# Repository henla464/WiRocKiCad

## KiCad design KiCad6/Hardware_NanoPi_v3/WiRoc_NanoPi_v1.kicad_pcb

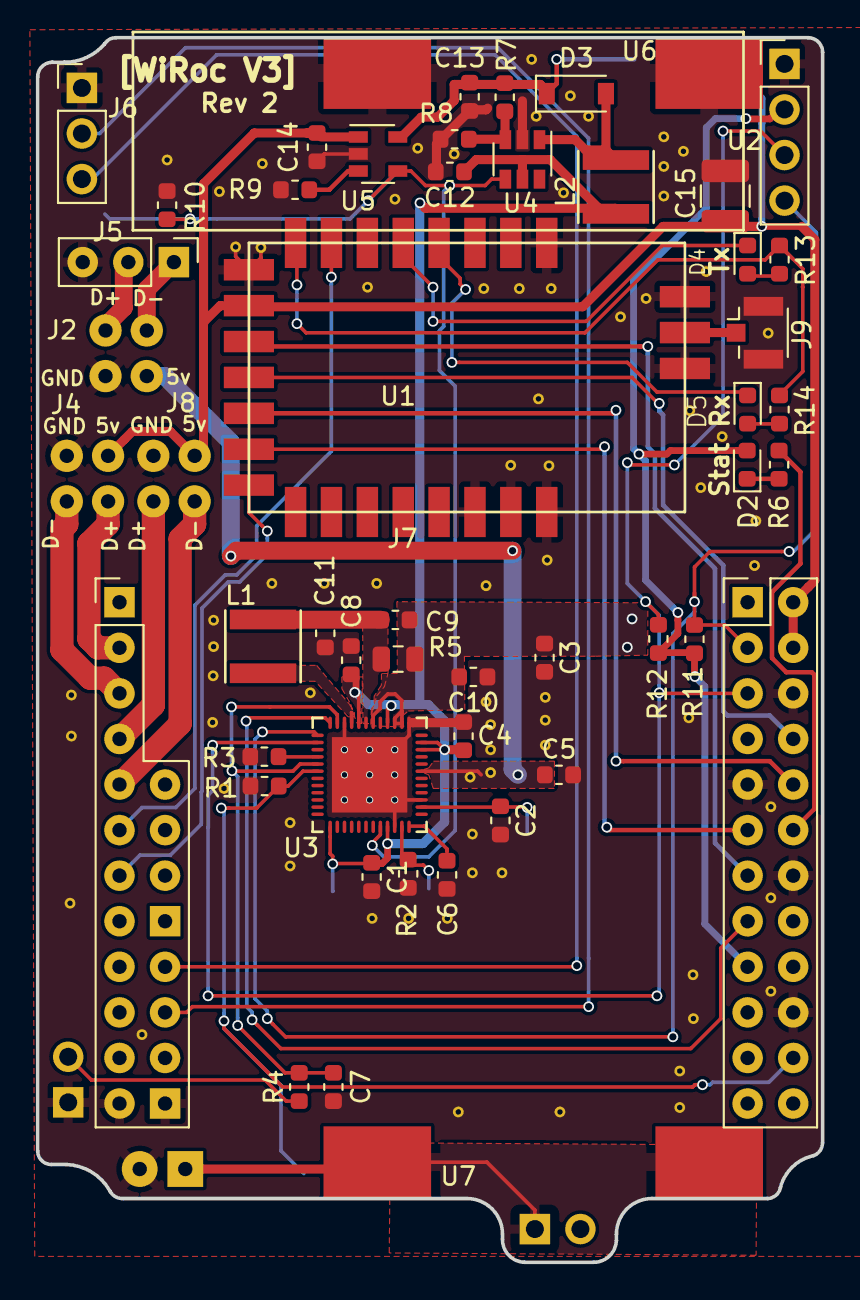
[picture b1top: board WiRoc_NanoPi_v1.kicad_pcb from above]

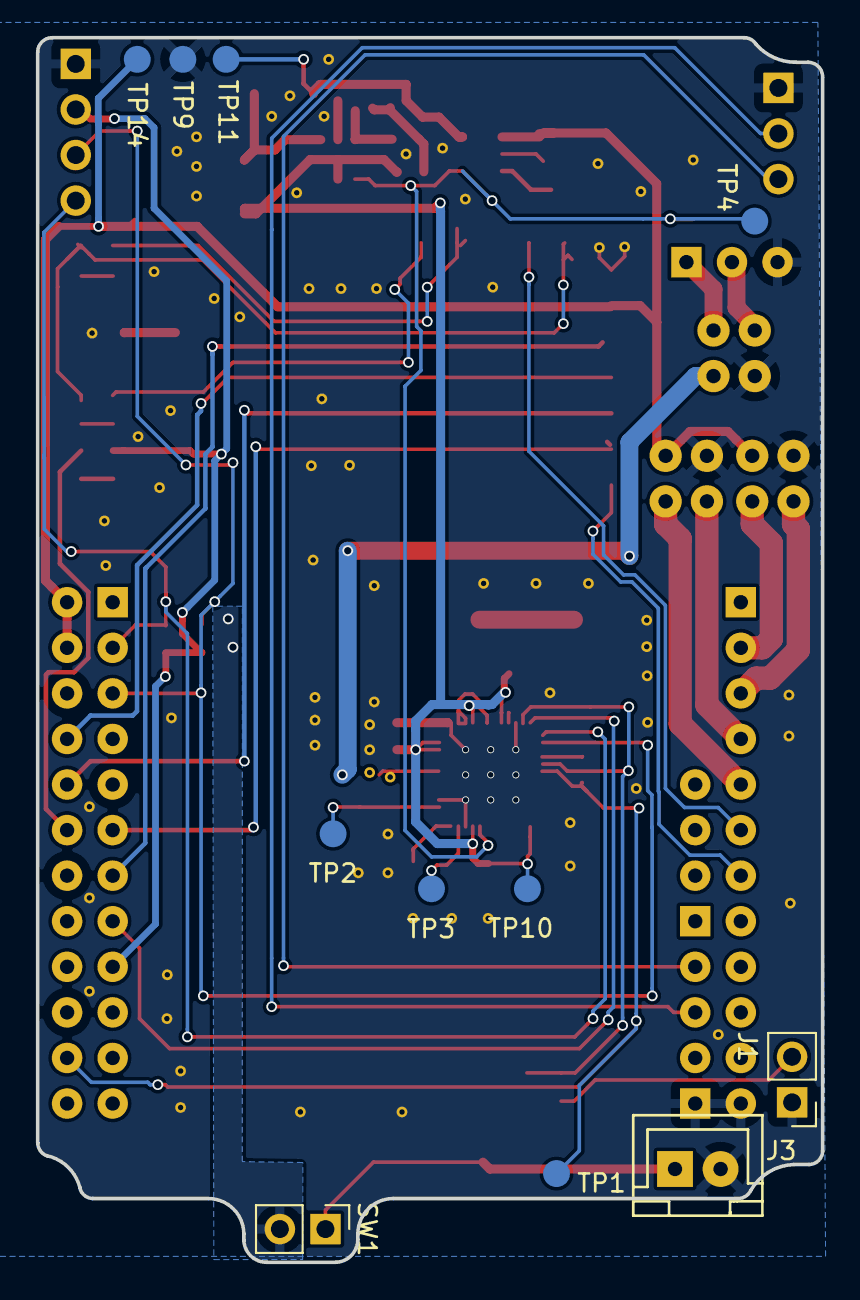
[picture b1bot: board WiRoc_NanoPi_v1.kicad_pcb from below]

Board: 2 copper layers, 43.8 x 68.3 mm, 60 parts (5 on the bottom side), 46 nets.

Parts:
C1, C3, C8, C10, C11: 4.7uF; C_0603_1608Metric
C2, C6, C9: 1uF; C_0603_1608Metric
C4, C5, C12, C13, C14: 10uF; C_0603_1608Metric
C7: 100pF; C_0603_1608Metric
C15: 47uF; C_1210_3225Metric
D2, D4, D5: LED; D_0603_1608Metric
D3: IN5819; D_SOD-123
J1: Conn_01x02; Pin_Header_Straight_1x02_Pitch2.54mm
J2: USB_Power_02x02; USBConnPads4
J3: JST-2PIN; JST_2.56
J4: USB_Host_Data_02x02; USBConnPads2
J5: Conn_01x03; Pin_Header_Straight_1x03_Pitch2.54mm
J6: HAT_Conn_DBG; Pin_Header_Straight_1x03_Pitch2.54mm
J7: NanoPIAir; NanoPiNeoAirAllPins
J8: USB_Host_Data_02x02; USBConnPads3
J9: Conn_Coaxial; U.FL_Hirose_U.FL-R-SMT-1_Vertical
L1, L2: 2.2uH-DCR<0.1R-1.5A; Inductor_SLW4018
R1, R10: 100K-1%; R_0603_1608Metric
R2, R3, R7: 200K-1%; R_0603_1608Metric
R4, R6, R13, R14: 1K; R_0603_1608Metric
R5: 0R03; R_0805_2012Metric
R8: 24K-1%; R_0603_1608Metric
R9: 3.6K-1%; R_0603_1608Metric
R11, R12: 10K; R_0603_1608Metric
SW1: SW_SPST; PinHeader_1x02_P2.54mm_Vertical
TP1, TP2, TP3, TP4, TP9, TP10, TP11, TP14: TEST; Measurement_Point_Round-SMD-Pad_Small
U1: DRF1268DS
U2: OLED; CONN_OLED_TWI-Socket_Strip_Straight_1x04_Pitch2.54mm
U3: AXP209; qfn48_6x6mm_Pitch0.4mm
U4: LP6226_SY7208; SOT-23-6
U5: SY6280; SOT-23-5
U6: BatteryPadM; BatteryPad
U7: BatteryPadP; BatteryPad

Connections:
BAT: C3.1, C9.1, C10.2, R5.2, SW1.2, U3.38, U3.39, U3.42
EXTEN: R10.2, TP4.1, U3.20, U4.4, U5.4
GND: C1.2, C2.2, C3.2, C4.2, C5.2, C6.2, C7.1, C8.1, C10.1, C11.1, C12.2, C13.2, C14.2, C15.1, J1.1, J2.4, J3.2, J4.4, J5.3, J6.1, J7.6, J7.9, J7.14, J7.20, J7.42, J7.51, J8.4, J9.2, R1.1, R2.1, R3.1, R8.1, R9.1, R10.1, TP9.1, U1.1, U1.9, U1.21, U1.22, U1.23, U1.24, U1.26, U2.1, U3.22, U3.27, U3.37, U3.46, U3.49, U4.2, U5.2, U6.1
IPSOUT: C1.1, C4.1, C8.2, C12.1, L2.1, TP10.1, U3.13, U3.21, U3.34, U3.35, U3.40, U3.44, U4.5
IRQ: J7.15, U3.48
LORAAUX: J7.11, U1.14
LORAEN: J7.13, U1.11
LORAMO: J7.37, U1.15
LORARS: J7.36, U1.7
N_VBUSEN: J7.22, R1.2, TP1.1, U3.6
unnamed: C2.1, TP2.1, U3.26
unnamed: C6.1, U3.24
unnamed: C9.2, C11.2, L1.2, R5.1, U3.43
unnamed: C13.1, D3.1, R7.2, TP11.1, U5.5
unnamed: D2.1, R6.1
unnamed: D3.2, L2.2, U4.1
unnamed: D4.1, U1.5
unnamed: D4.2, R13.1
unnamed: D5.1, U1.4
unnamed: D5.2, R14.1
unnamed: J1.2, R4.1
unnamed: J2.2, J5.1
unnamed: J2.3, J5.2
unnamed: J3.1, SW1.1, U7.1
unnamed: J6.2, J7.53
unnamed: J6.3, J7.54
unnamed: J9.1, U1.25
unnamed: L1.1, U3.45
unnamed: R2.2, TP3.1, U3.23
unnamed: R3.2, U3.4
unnamed: R7.1, R8.2, U4.3
unnamed: R9.2, U5.3
unnamed: R13.2, R14.2, U1.8
PWRON: C7.2, R4.2, U3.5, U3.47
SCK: J7.5, R12.1, U2.3, U3.2
SDA: J7.3, R11.1, U2.4, U3.1
STATUS_LED: J7.12, R6.2
SYS_3.3V: D2.2, J7.17, R11.2, R12.2, U2.2
UART1_RX: J7.10, U1.13
UART1_TX: J7.8, U1.12
USBHost-DM1: J4.2, J7.33
USBHost-DM2: J7.35, J8.2
USBHost-DP1: J4.3, J7.32
USBHost-DP2: J7.34, J8.3
VBUS: C5.1, J2.1, U3.31
VDD_5V: C14.1, C15.2, J4.1, J7.2, J7.4, J8.1, TP14.1, U1.10, U5.1

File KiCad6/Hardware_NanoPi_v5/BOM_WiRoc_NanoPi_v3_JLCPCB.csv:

Designator,Comment,Footprint,Comment2,LCSC Part #,Package
C13 C12 C14 C4 C5 ,10uF,Capacitor_SMD:C_0603_1608Metric, ,C19702,603
C3 ,4.7uF,Capacitor_SMD:C_0603_1608Metric, ,C19666,603
C9 C2 C6 ,1uF,Capacitor_SMD:C_0603_1608Metric, ,C15849,603
C11 C10 C8 C1 ,4.7uF,Capacitor_SMD:C_0603_1608Metric, ,C19666,603
C7 ,100pF,Capacitor_SMD:C_0603_1608Metric,100pF (101) ±5% 50V,C14858,603
C15 ,47uF,Capacitor_SMD:C_1210_3225Metric, ,C77101,1210
D3 ,IN5819,Diode_SMD:D_SOD-123,Diode Schottky 40V 1A Surface Mount SOD-123,C8597,SOD-123
D2 D5 D4 ,LED,Diode_SMD:D_0603_1608Metric,Red LED,C2286,603
J9 ,Conn_Coaxial,Connector_Coaxial:U.FL_Hirose_U.FL-R-SMT-1_Vertical, ,C88374, 
L2 L1 ,2.2uH-DCR<0.1R-1.5A,WiRoc:Inductor_SLW4018,FIXED IND 2.2UH 1.7A 55 MOHM SMD,C206341,4018
R7 R2 R3 ,200K-1%,Resistor_SMD:R_0603_1608Metric, ,C25811,603
R8 ,24K-1%,Resistor_SMD:R_0603_1608Metric, ,C23352,603
R9 ,3.6K-1%,Resistor_SMD:R_0603_1608Metric, ,C22980,603
R5 ,0R03,Resistor_SMD:R_0805_2012Metric,RESISTOR 0805 0.03Ω 1/8W±1%,C247605,805
R4 R6 R14 R13 ,1K,Resistor_SMD:R_0603_1608Metric,1KΩ (1001) ±1%,C21190,603
R1 R10 ,100K-1%,Resistor_SMD:R_0603_1608Metric, ,C25803,603
R11 R12 ,10K,Resistor_SMD:R_0603_1608Metric,RESISTOR 0603 10KΩ,C25804,603
U3 ,AXP209,WiRoc:qfn48_6x6mm_Pitch0.4mm,Enhanced single Cell Li-Battery and Power System Management IC,C80525,6mm x 6mm 48-pin QFN
U4 ,LP6226_SY7208,TO_SOT_Packages_SMD:SOT-23-6,High Efficiency Boost DC/DC Convertor,C80514,SOT23-6
U5 ,SY6280,TO_SOT_Packages_SMD:SOT-23-5,Power Distribution Switch  1In/1Out  Act-High Enable  1A  Vin 2.4÷5.5V  80mΩ,C55136,SOT23-5

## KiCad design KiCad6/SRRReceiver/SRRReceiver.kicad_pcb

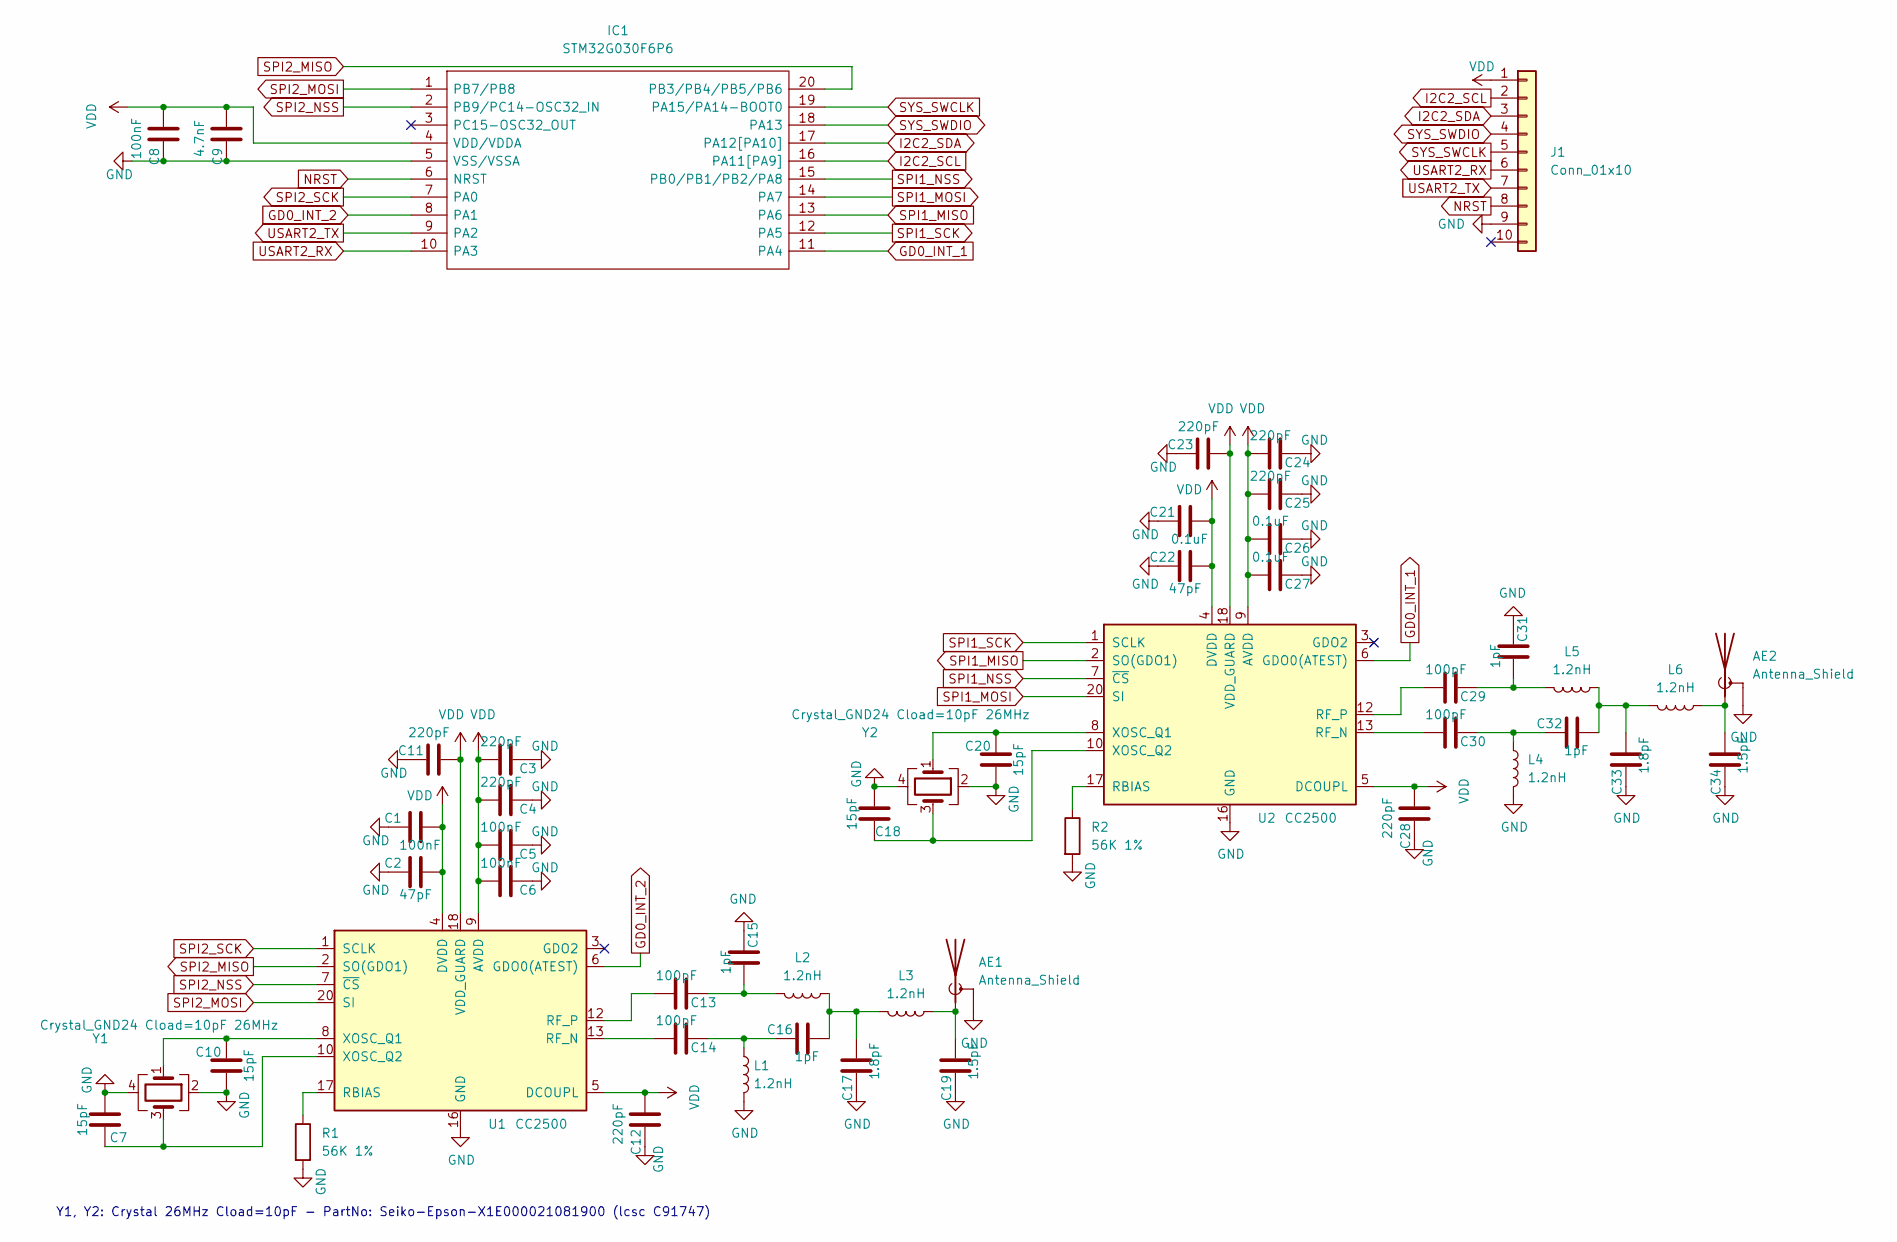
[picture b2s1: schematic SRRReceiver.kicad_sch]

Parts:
AE1, AE2: Antenna_Shield; Texas_SWRA117D_2.4GHz_Right
C1, C5, C6, C8: 100nF; C_0402_1005Metric; LCSC C1525
C2, C22: 47pF; C_0402_1005Metric; LCSC C1567
C3, C4, C11, C12, C23, C24, C25, C28: 220pF; C_0402_1005Metric; LCSC C16772
C7, C10, C18, C20: 15pF; C_0402_1005Metric; LCSC C1548
C9: 4.7nF; C_0402_1005Metric; LCSC C1538
C13, C14, C29, C30: 100pF; C_0402_1005Metric; LCSC C1546
C15, C16, C31, C32: 1pF; C_0402_1005Metric; LCSC C1550
C17, C33: 1.8pF; C_0402_1005Metric; LCSC C76902
C19, C34: 1.5pF; C_0402_1005Metric; LCSC C282238
C21, C26, C27: 0.1uF; C_0402_1005Metric; LCSC C1525
IC1: STM32G030F6P6; SOP65P640X120-20N; Manufacturer_Part_Number STM32G030F6P6; Mouser Part Number 511-STM32G030F6P6
J1: Conn_01x10; FPC-Connector_1x10-1MP_P0.5mm_Horizontal
L1, L2, L3, L4, L5, L6: 1.2nH; L_0402_1005Metric; LCSC C77117
R1, R2: 56K 1%; R_0402_1005Metric; LCSC C25796
U1, U2: CC2500; Texas_S-PVQFN-N20_EP2.4x2.4mm; LCSC C57494
Y1, Y2: Crystal_GND24 Cload=10pF 26MHz; Crystal_SMD_3225-4Pin_3.2x2.5mm; LCSC C91747

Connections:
GD0_INT_1: IC1.11 (PA4), U2.6 (GDO0(ATEST))
GD0_INT_2: IC1.8 (PA1), U1.6 (GDO0(ATEST))
GND: AE1.2 (Shield), AE2.2 (Shield), C1.1, C2.1, C3.1, C4.1, C5.1, C6.1, C7.1, C8.1, C9.1, C10.1, C11.1, C12.1, C15.1, C17.1, C18.1, C19.1, C20.1, C21.1, C22.1, C23.1, C24.1, C25.1, C26.1, C27.1, C28.1, C31.1, C33.1, C34.1, IC1.5 (VSS/VSSA), J1.9, L1.2, L4.2, R1.2, R2.2, U1.16 (GND), U1.19 (GND), U1.21 (GND), U2.16 (GND), U2.19 (GND), U2.21 (GND), Y1.2, Y1.4, Y2.2, Y2.4
I2C2_SCL: IC1.16 (PA11[PA9]), J1.2
I2C2_SDA: IC1.17 (PA12[PA10]), J1.3
NRST: IC1.6 (NRST), J1.8
unnamed: AE1.1 (A), C19.2, L3.1
unnamed: AE2.1 (A), C34.2, L6.1
unnamed: C7.2, U1.10 (XOSC_Q2), Y1.3
unnamed: C10.2, U1.8 (XOSC_Q1), Y1.1
unnamed: C13.1, C15.2, L2.2
unnamed: C13.2, U1.12 (RF_P)
unnamed: C14.1, C16.1, L1.1
unnamed: C14.2, U1.13 (RF_N)
unnamed: C16.2, C17.2, L2.1, L3.2
unnamed: C18.2, U2.10 (XOSC_Q2), Y2.3
unnamed: C20.2, U2.8 (XOSC_Q1), Y2.1
unnamed: C29.1, C31.2, L5.2
unnamed: C29.2, U2.12 (RF_P)
unnamed: C30.1, C32.1, L4.1
unnamed: C30.2, U2.13 (RF_N)
unnamed: C32.2, C33.2, L5.1, L6.2
unnamed: R1.1, U1.17 (RBIAS)
unnamed: R2.1, U2.17 (RBIAS)
SPI1_MISO: IC1.13 (PA6), U2.2 (SO(GDO1))
SPI1_MOSI: IC1.14 (PA7), U2.20 (SI)
SPI1_NSS: IC1.15 (PB0/PB1/PB2/PA8), U2.7 (~CS)
SPI1_SCK: IC1.12 (PA5), U2.1 (SCLK)
SPI2_MISO: IC1.20 (PB3/PB4/PB5/PB6), U1.2 (SO(GDO1))
SPI2_MOSI: IC1.1 (PB7/PB8), U1.20 (SI)
SPI2_NSS: IC1.2 (PB9/PC14-OSC32_IN), U1.7 (~CS)
SPI2_SCK: IC1.7 (PA0), U1.1 (SCLK)
SYS_SWCLK: IC1.19 (PA15/PA14-BOOT0), J1.5
SYS_SWDIO: IC1.18 (PA13), J1.4
USART2_RX: IC1.10 (PA3), J1.6
USART2_TX: IC1.9 (PA2), J1.7
VDD: C1.2, C2.2, C3.2, C4.2, C5.2, C6.2, C8.2, C9.2, C11.2, C12.2, C21.2, C22.2, C23.2, C24.2, C25.2, C26.2, C27.2, C28.2, IC1.4 (VDD/VDDA), J1.1, U1.4 (DVDD), U1.5 (DCOUPL), U1.9 (AVDD), U1.11 (AVDD), U1.14 (AVDD), U1.15 (AVDD), U1.18 (VDD_GUARD), U2.4 (DVDD), U2.5 (DCOUPL), U2.9 (AVDD), U2.11 (AVDD), U2.14 (AVDD), U2.15 (AVDD), U2.18 (VDD_GUARD)

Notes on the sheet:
Y1, Y2: Crystal 26MHz Cload=10pF - PartNo: Seiko-Epson-X1E000021081900 (lcsc C91747)

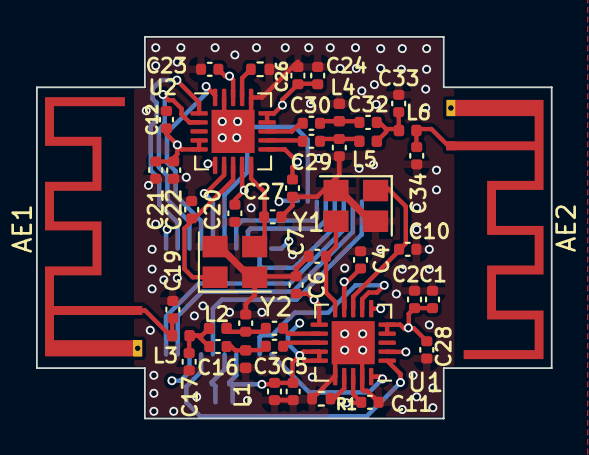
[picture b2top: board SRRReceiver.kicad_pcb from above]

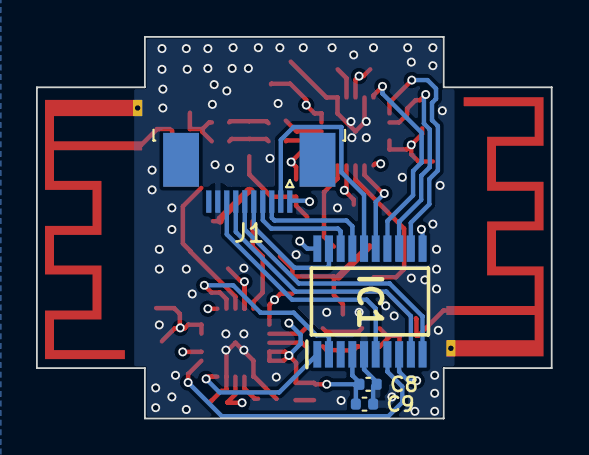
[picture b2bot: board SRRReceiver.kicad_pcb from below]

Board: 4 copper layers, 28.6 x 21.2 mm, 50 parts (4 on the bottom side), 37 nets.

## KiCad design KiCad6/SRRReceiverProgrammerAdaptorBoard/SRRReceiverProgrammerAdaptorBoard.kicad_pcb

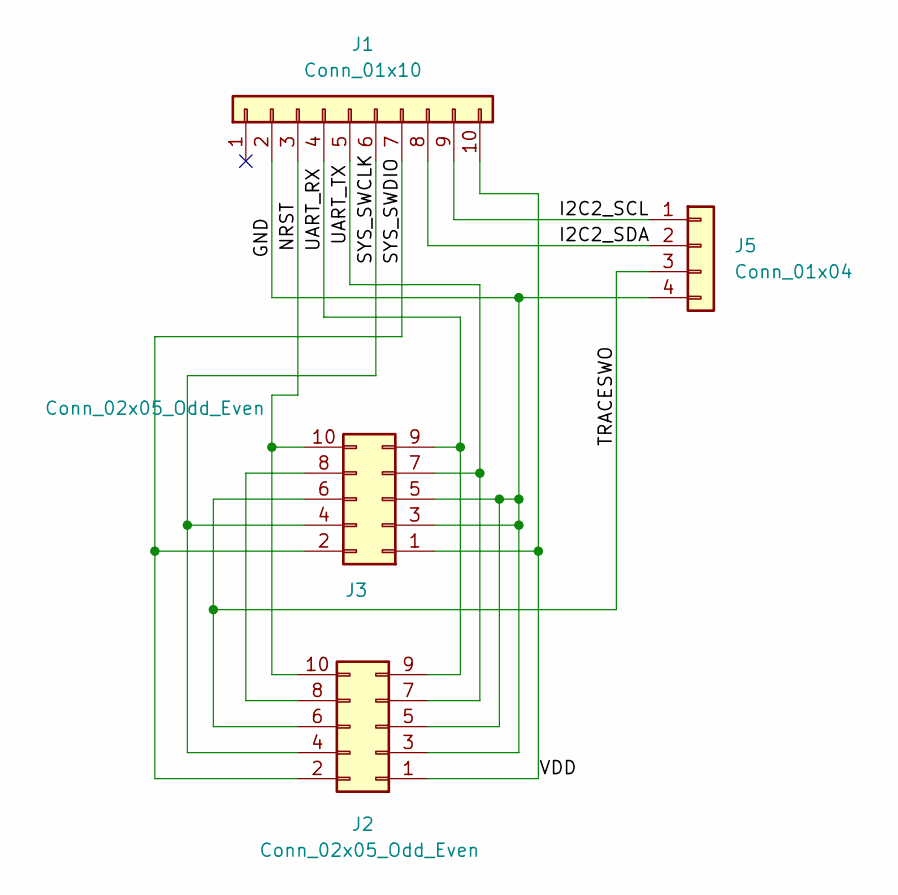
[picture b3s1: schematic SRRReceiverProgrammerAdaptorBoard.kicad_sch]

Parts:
J1: Conn_01x10; FPC-Connector_1x10-1MP_P0.5mm_Horizontal
J2, J3: Conn_02x05_Odd_Even; PinHeader_2x05_P1.27mm_Vertical
J5: Conn_01x04; PinHeader_1x04_P2.54mm_Vertical

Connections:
/GND: J1.2, J2.3, J2.5, J3.3, J3.5, J5.4
/I2C2_SCL: J1.9, J5.1
/I2C2_SDA: J1.8, J5.2
/NRST: J1.3, J2.10, J3.10
/SYS_SWCLK: J1.6, J2.4, J3.4
/SYS_SWDIO: J1.7, J2.2, J3.2
/TRACESWO: J2.6, J3.6, J5.3
/UART_RX: J1.4, J2.9, J3.9
/UART_TX: J1.5, J2.7, J3.7
/VDD: J1.10, J2.1, J3.1
unnamed: J2.8, J3.8

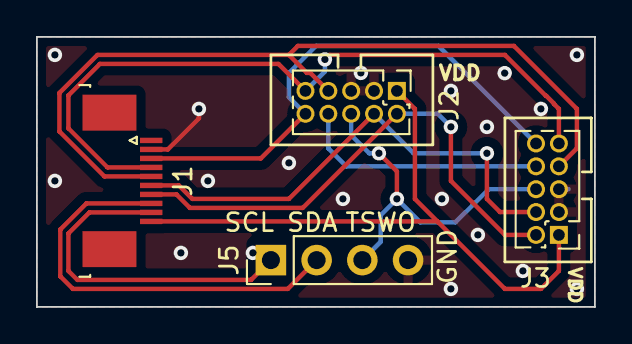
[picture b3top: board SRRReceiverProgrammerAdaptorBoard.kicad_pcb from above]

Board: 2 copper layers, 31.0 x 15.0 mm, 4 parts (0 on the bottom side), 11 nets.

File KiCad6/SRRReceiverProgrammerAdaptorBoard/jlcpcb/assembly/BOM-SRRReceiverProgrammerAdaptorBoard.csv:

Comment,Designator,Footprint,LCSC
Conn_02x05_Odd_Even,J3,PinHeader_2x05_P1.27mm_Vertical,
Conn_02x05_Odd_Even,J2,PinHeader_2x05_P1.27mm_Vertical,
Conn_01x10,J1,FPC-Connector_1x10-1MP_P0.5mm_Horizontal,
Conn_01x04,J5,PinHeader_1x04_P2.54mm_Vertical,

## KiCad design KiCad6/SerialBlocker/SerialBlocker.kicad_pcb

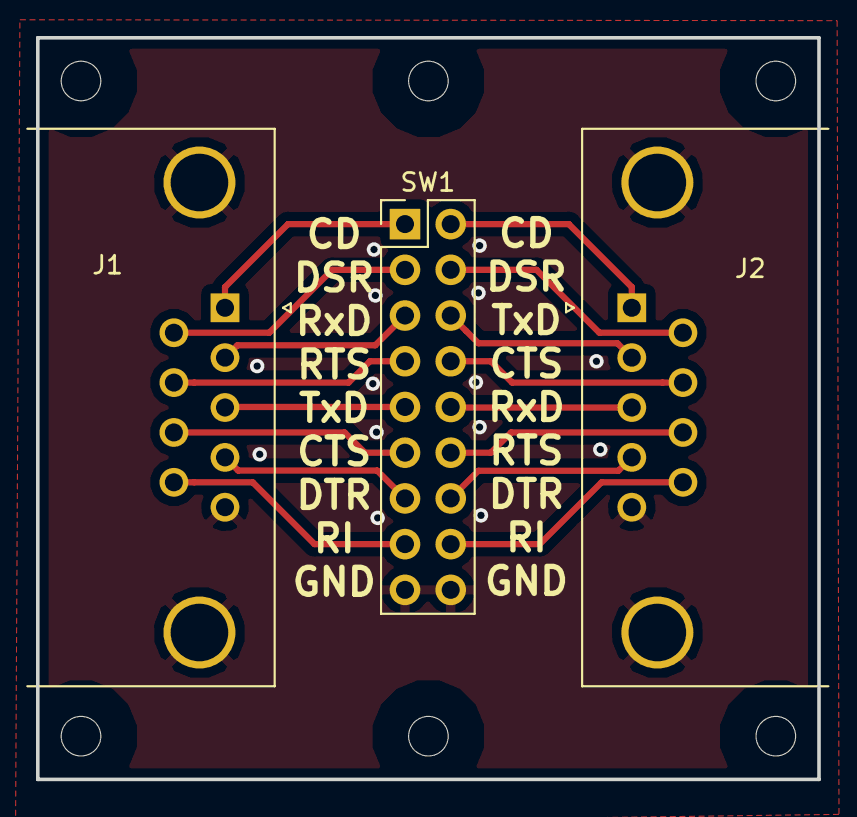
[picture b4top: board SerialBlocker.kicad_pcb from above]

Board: 2 copper layers, 43.4 x 41.2 mm, 3 parts (0 on the bottom side), 17 nets.

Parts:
J1: DB9_Male_MountingHoles; DSUB-9_Male_Horizontal_P2.77x2.84mm_Edge_Housed_MountingHol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
J2: DB9_Female_MountingHoles; DSUB-9_Female_Horizontal_P2.77x2.84mm_Edge_offset6.96mm_cen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
SW1: SW_DIP_x09; PinHeader_Serial_Blocker

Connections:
GND: J1.0, J1.5, J2.0, J2.5, SW1.9, SW1.10
unnamed: J1.1, SW1.1
unnamed: J1.2, SW1.3
unnamed: J1.3, SW1.5
unnamed: J1.4, SW1.7
unnamed: J1.6, SW1.2
unnamed: J1.7, SW1.4
unnamed: J1.8, SW1.6
unnamed: J1.9, SW1.8
unnamed: J2.1, SW1.18
unnamed: J2.2, SW1.16
unnamed: J2.3, SW1.14
unnamed: J2.4, SW1.12
unnamed: J2.6, SW1.17
unnamed: J2.7, SW1.15
unnamed: J2.8, SW1.13
unnamed: J2.9, SW1.11

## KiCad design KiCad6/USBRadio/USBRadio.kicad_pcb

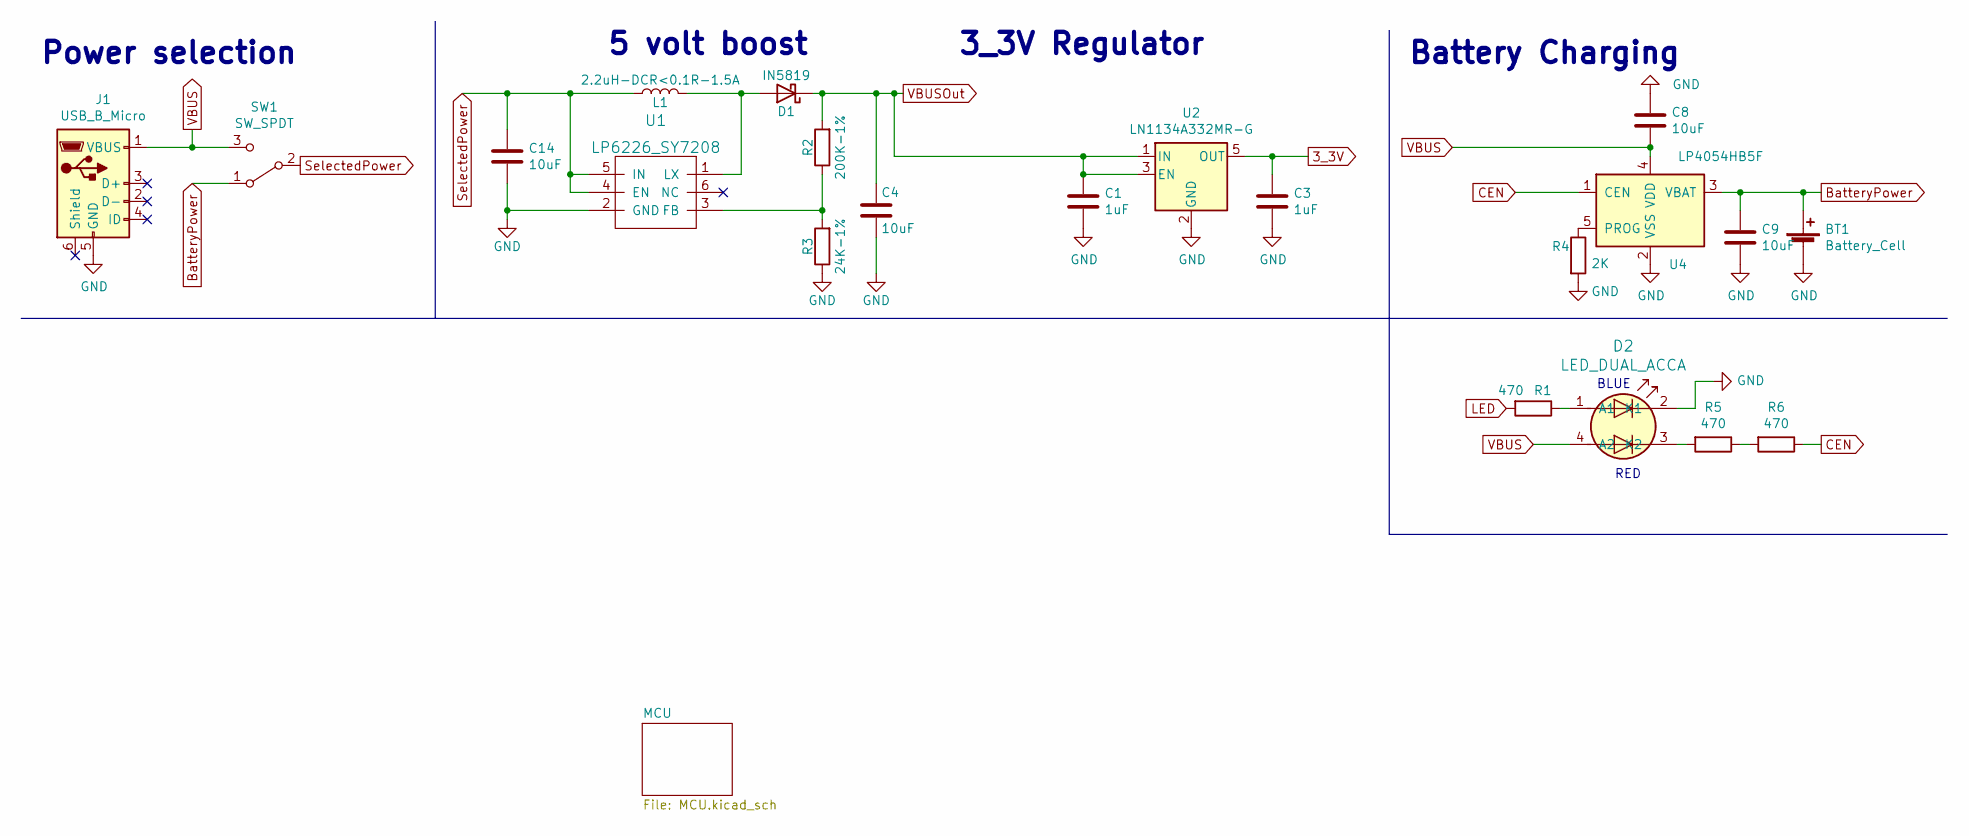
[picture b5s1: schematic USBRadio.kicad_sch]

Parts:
BT1: Battery_Cell; JST_2.56
C1, C3: 1uF; C_0603_1608Metric_Pad1.08x0.95mm_HandSolder; ManufacturerPartNumber CL10A105KB8NNNC; LCSC Part # C15849
C4, C8, C9, C14: 10uF; C_0603_1608Metric_Pad1.08x0.95mm_HandSolder; ManufacturerPartNumber CL10A106KP8NNNC; LCSC Part # C19702
D1: IN5819; D_SOD-123; ManufacturerPartNumber B5817W; LCSC Part # C8597
D2: LED_DUAL_ACCA; LED_Dual_1.7_1.6; ManufacturerPartNumber HL-PCB-1617S9FH203BC; LCSC Part # C513363
J1: USB_B_Micro; USB_Micro-B_Horizontal; ManufacturerPartNumber U254-051T-4BH83-F1S; LCSC Part # C397452
L1: 2.2uH-DCR<0.1R-1.5A; Inductor_SLW4018; ManufacturerPartNumber SLW4018S2R2MST; LCSC Part # C206341
R1, R5, R6: 470; R_0805_2012Metric_Pad1.20x1.40mm_HandSolder; ManufacturerPartNumber 0805W8F4700T5E; LCSC Part # C17710
R2: 200K-1%; C_0603_1608Metric_Pad1.08x0.95mm_HandSolder; ManufacturerPartNumber 0603WAF2003T5E; LCSC Part # C25811
R3: 24K-1%; C_0603_1608Metric_Pad1.08x0.95mm_HandSolder; ManufacturerPartNumber 0603WAF2402T5E; LCSC Part # C23352
R4: 2K; R_0805_2012Metric_Pad1.20x1.40mm_HandSolder; ManufacturerPartNumber 0805W8F2001T5E; LCSC Part # C17604
SW1: SW_SPDT; SW_SPDT_PCM12; ManufacturerPartNumber SK-3296S-01-L3; LCSC Part # C319019
U1: LP6226_SY7208; TSOT-23-6_HandSoldering; ManufacturerPartNumber SY7208ABC; LCSC Part # C80514
U2: LN1134A332MR-G; SOT-23-5; ManufacturerPartNumber LN1134A332MR-G; LCSC Part # C141419
U4: LP4054HB5F; SOT-23-5; ManufacturerPartNumber LP4054HB5F; LCSC Part # C517187

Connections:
3_3V: C3.1, U2.5 (OUT); also elsewhere on the board
BatteryPower: BT1.1 (+), C9.1, SW1.1 (A), U4.3 (VBAT)
CEN: R6.1, U4.1 (CEN)
GND: BT1.2 (-), C1.2, C3.2, C4.2, C8.1, C9.2, C14.2, D2.2 (K1), J1.5 (GND), R3.1, R4.2, U1.2 (GND), U2.2 (GND), U4.2 (VSS); also elsewhere on the board
LED: R1.2; also elsewhere on the board
unnamed: D1.2 (A), L1.2, U1.1 (LX)
unnamed: D2.1 (A1), R1.1
unnamed: D2.3 (K2), R5.2
unnamed: R2.1, R3.2, U1.3 (FB)
unnamed: R4.1, U4.5 (PROG)
unnamed: R5.1, R6.2
SelectedPower: C14.1, L1.1, SW1.2 (B), U1.4 (EN), U1.5 (IN)
VBUS: C8.2, D2.4 (A2), J1.1 (VBUS), SW1.3 (C), U4.4 (VDD)
VBUSOut: C1.1, C4.1, D1.1 (K), R2.2, U2.1 (IN), U2.3 (EN); also elsewhere on the board

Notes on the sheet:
RED
Power selection
BLUE
5 volt boost
3_3V Regulator
Battery Charging

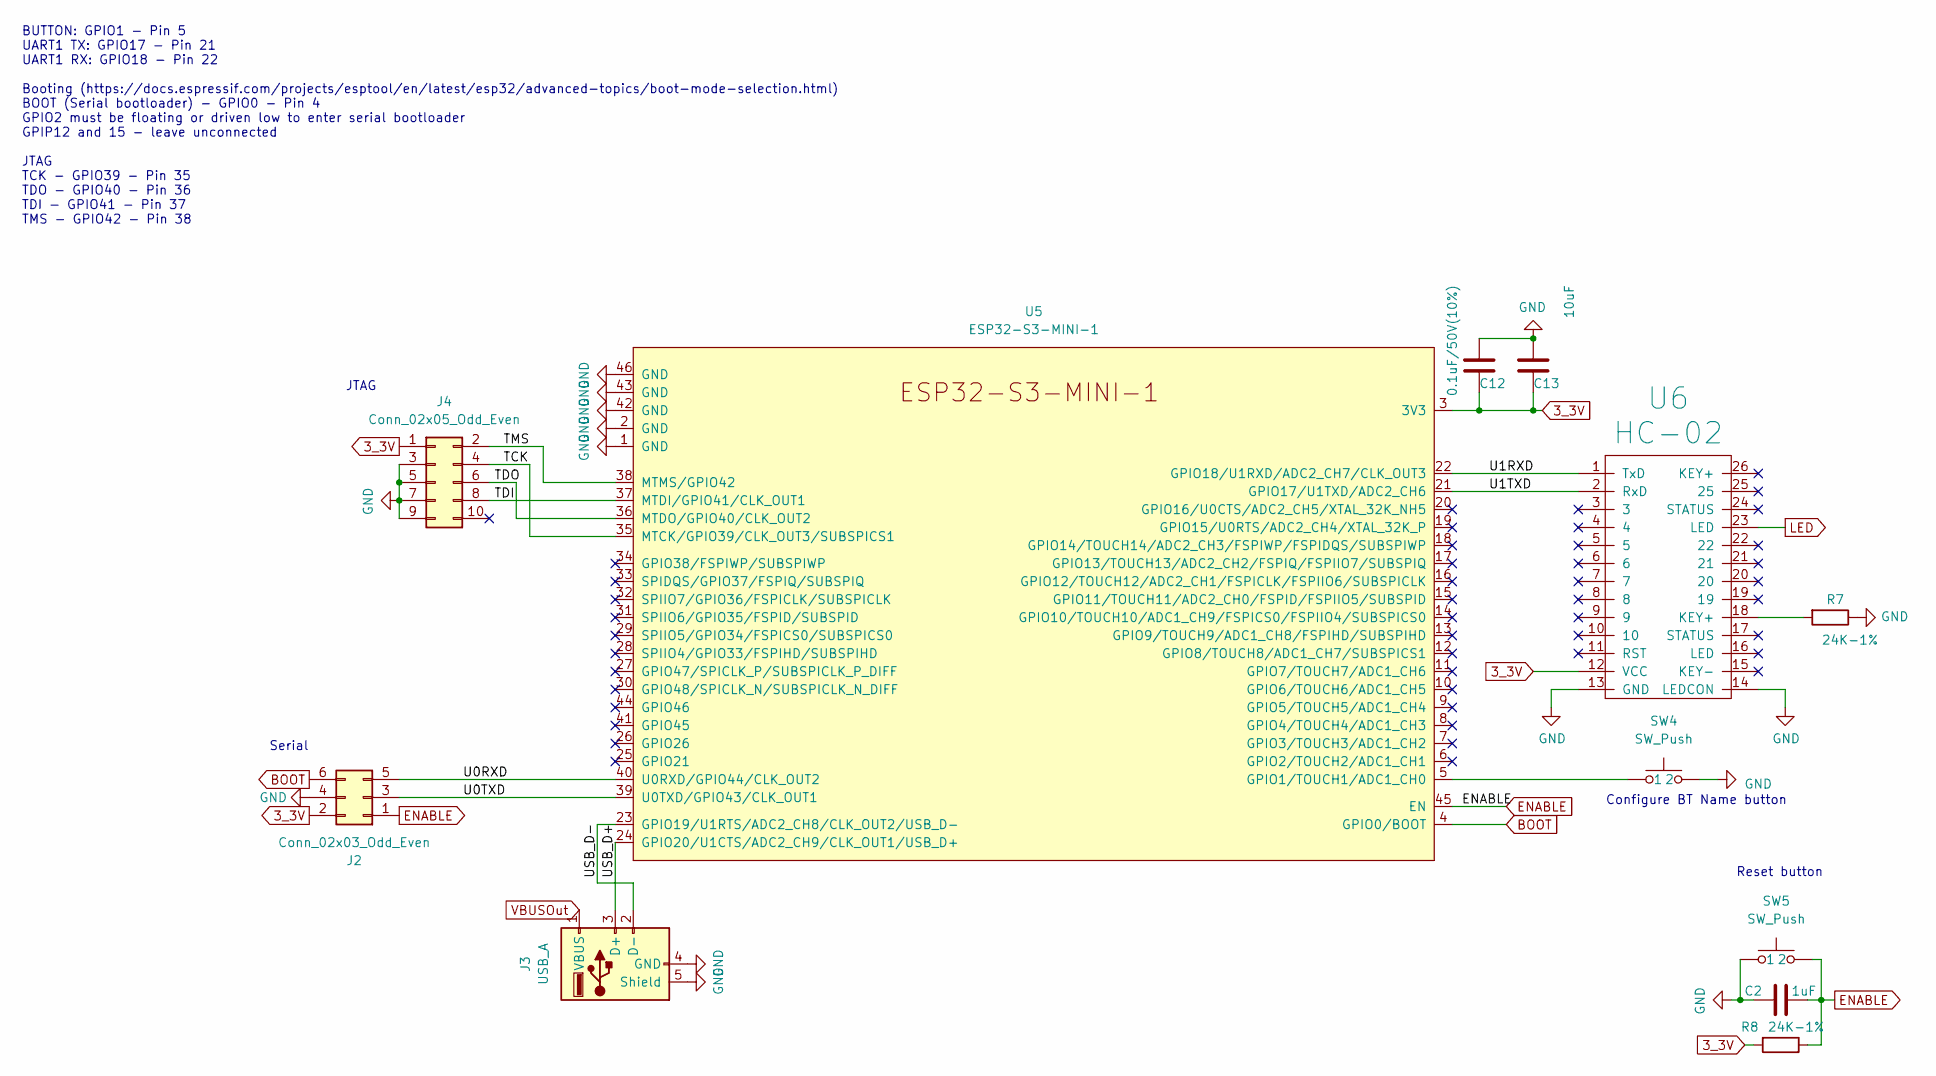
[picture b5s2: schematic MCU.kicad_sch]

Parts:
C2: 1uF; C_0603_1608Metric_Pad1.08x0.95mm_HandSolder; ManufacturerPartNumber CL10A105KB8NNNC; LCSC Part # C15849
C12: 0.1uF/50V(10%); C_0805_2012Metric_Pad1.18x1.45mm_HandSolder; ManufacturerPartNumber CC0805KRX7R9BB104; LCSC Part # C49678
C13: 10uF; C_0603_1608Metric_Pad1.08x0.95mm_HandSolder; ManufacturerPartNumber CL10A106KP8NNNC; LCSC Part # C19702
J2: Conn_02x03_Odd_Even; IDC-Header_2x03_P1.27mm_Vertical_SMD
J3: USB_A; USB_A_CONNFLY_DS1095-WNR0
J4: Conn_02x05_Odd_Even; IDC-Header_2x05_P1.27mm_Vertical_SMD
R7, R8: 24K-1%; C_0603_1608Metric_Pad1.08x0.95mm_HandSolder; ManufacturerPartNumber 0603WAF2402T5E; LCSC Part # C23352
SW4, SW5: SW_Push; SW_SPST_TL3342; ManufacturerPartNumber TS-1187A-B-A-B; LCSC Part # C318884
U5: ESP32-S3-MINI-1
U6: HC-02

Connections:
3_3V: C12.1, C13.1, J2.2, J4.1, R8.2, U5.3 (3V3), U6.12 (VCC); also elsewhere on the board
/MCU/TCK: J4.4, U5.35 (MTCK/GPIO39/CLK_OUT3/SUBSPICS1)
/MCU/TDI: J4.8, U5.37 (MTDI/GPIO41/CLK_OUT1)
/MCU/TDO: J4.6, U5.36 (MTDO/GPIO40/CLK_OUT2)
/MCU/TMS: J4.2, U5.38 (MTMS/GPIO42)
/MCU/U0RXD: J2.5, U5.40 (U0RXD/GPIO44/CLK_OUT2)
/MCU/U0TXD: J2.3, U5.39 (U0TXD/GPIO43/CLK_OUT1)
/MCU/U1RXD: U5.22 (GPIO18/U1RXD/ADC2_CH7/CLK_OUT3), U6.1 (TxD)
/MCU/U1TXD: U5.21 (GPIO17/U1TXD/ADC2_CH6), U6.2 (RxD)
/MCU/USB_D+: J3.3 (D+), U5.24 (GPIO20/U1CTS/ADC2_CH9/CLK_OUT1/USB_D+)
/MCU/USB_D-: J3.2 (D-), U5.23 (GPIO19/U1RTS/ADC2_CH8/CLK_OUT2/USB_D-)
BOOT: J2.6, U5.4 (GPIO0/BOOT)
ENABLE: C2.2, J2.1, R8.1, SW5.2, U5.45 (EN)
GND: C2.1, C12.2, C13.2, J2.4, J3.4 (GND), J3.5 (Shield), J4.3, J4.5, J4.7, J4.9, R7.1, SW4.2, SW5.1, U5.1 (GND), U5.2 (GND), U5.42 (GND), U5.43 (GND), U5.46 (GND), U6.13 (GND), U6.14 (LEDCON); also elsewhere on the board
LED: U6.23 (LED); also elsewhere on the board
unnamed: R7.2, U6.18 (KEY+)
unnamed: SW4.1, U5.5 (GPIO1/TOUCH1/ADC1_CH0)
VBUSOut: J3.1 (VBUS); also elsewhere on the board

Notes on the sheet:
Reset button
JTAG
BUTTON: GPIO1 - Pin 5 UART1 TX: GPIO17 - Pin 21 UART1 RX: GPIO18 - Pin 22 Booting (https://docs.espressif.com/projects/esptool/en/latest/esp32/advanced-topics/boot-mode-selection.html) BOOT (Serial bootloader) - GPIO0 - Pin 4 GPIO2 must be floating or driven low to enter serial bootloader GPIP12 an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
Serial
Configure BT Name button

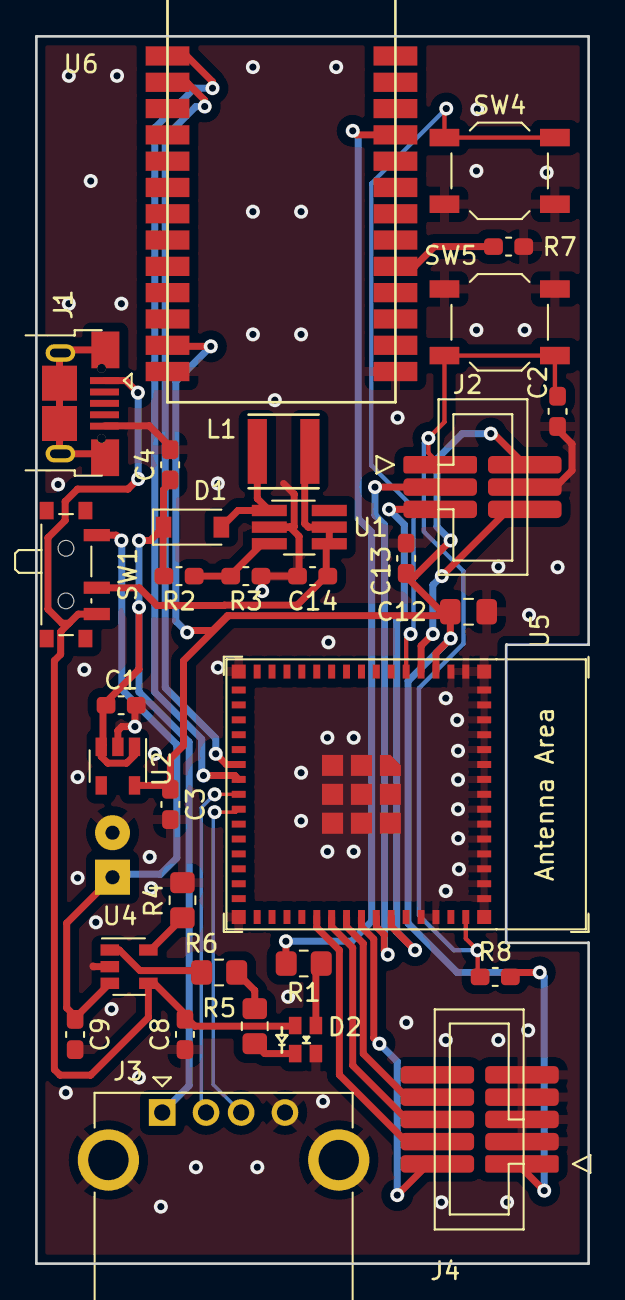
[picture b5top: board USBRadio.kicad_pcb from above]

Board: 2 copper layers, 31.5 x 70.0 mm, 33 parts (1 on the bottom side), 28 nets.
